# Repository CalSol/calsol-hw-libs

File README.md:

# calsol-hw-libs
CalSol's shared libraries for hardware -- KiCAD libraries and footprints.

## Repository Structure
This is meant to be [submoduled](https://git-scm.com/book/en/v2/Git-Tools-Submodules) into a higher-level project.

- [layout.pretty] - Footprints go here.
- [schematic] - Schematic elements go here.
- [schematic_kicad] - This is a dump of the current KiCAD library set. Don't change these unless you have a compelling reason to (ie. the KiCAD libraries have been updated)

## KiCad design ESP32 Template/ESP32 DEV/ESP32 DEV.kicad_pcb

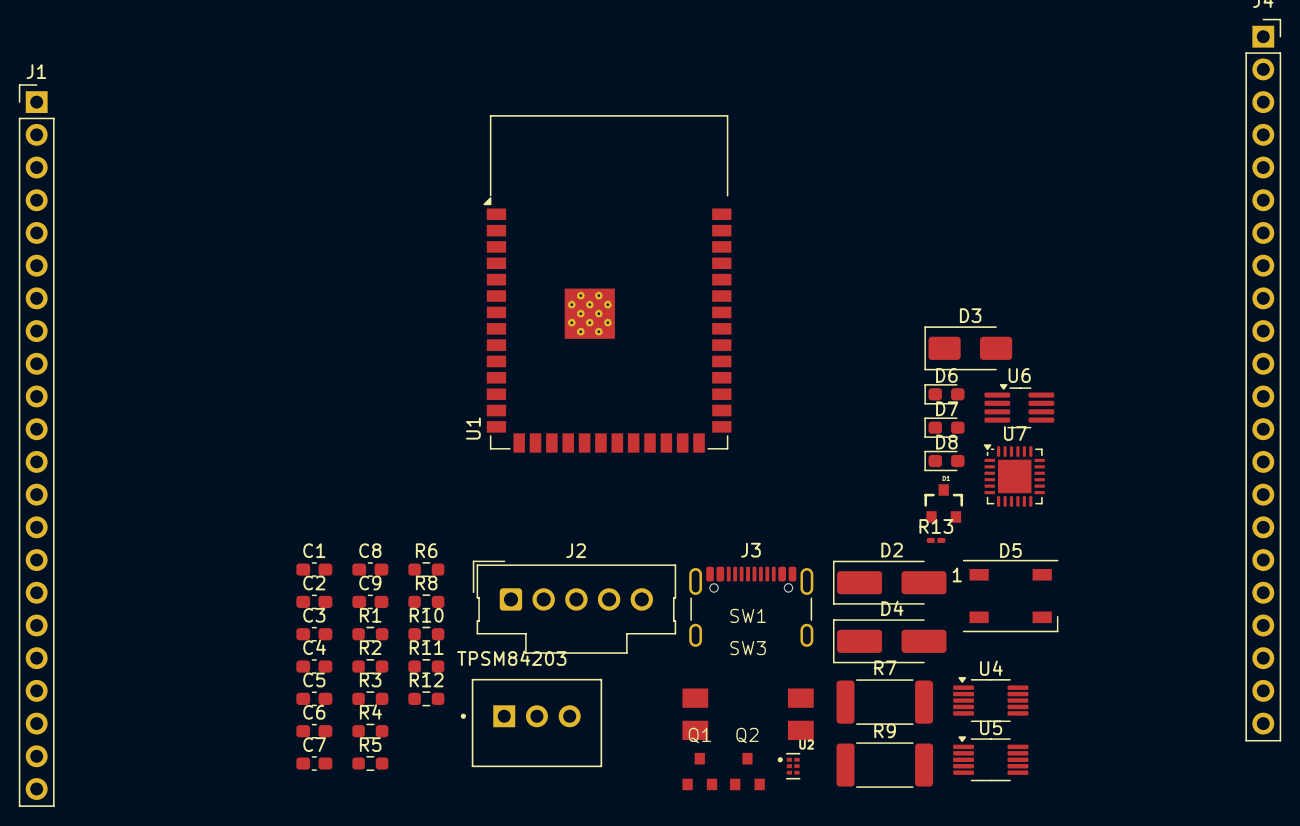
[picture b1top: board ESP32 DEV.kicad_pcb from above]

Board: 2 copper layers, 45 parts (0 on the bottom side), 61 nets, no tracks yet.

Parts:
C1, C8: 100uF; C_0603_1608Metric_Pad1.08x0.95mm_HandSolder
C2, C4, C5, C7: 0.1uF; C_0603_1608Metric_Pad1.08x0.95mm_HandSolder
C3, C6: 10uF; C_0603_1608Metric_Pad1.08x0.95mm_HandSolder
C9: 1uF; C_0603_1608Metric_Pad1.08x0.95mm_HandSolder
D1: PESD1CAN; SOT23-3
D2, D4: D; D_SMA_Handsoldering
D3: SMAJ26CA; D_SMA
D5: WS2812B; LED_WS2812B_PLCC4_5.0x5.0mm_P3.2mm
D6, D7, D8: LED; LED_0603_1608Metric_Pad1.05x0.95mm_HandSolder
J1: Conn_01x22_Pin; PinHeader_1x22_P2.54mm_Vertical
J2: Conn_01x05_Socket; Molex_SL_171971-0005_1x05_P2.54mm_Vertical
J3: USB_C_Receptacle_USB2.0_14P; USB_C_Receptacle_GCT_USB4105-xx-A_16P_TopMnt_Horizontal
J4: Conn_01x22_Pin; PinSocket_1x22_P2.54mm_Vertical
Q1, Q2: NPN; SS8050
R1, R2: 5.1k; R_0603_1608Metric_Pad0.98x0.95mm_HandSolder
R3: 10; R_0603_1608Metric_Pad0.98x0.95mm_HandSolder
R4, R5, R10, R11: 10k; R_0603_1608Metric_Pad0.98x0.95mm_HandSolder
R6: 1k; R_0603_1608Metric_Pad0.98x0.95mm_HandSolder
R7, R9: 0.02; R_2512_6332Metric_Pad1.40x3.35mm_HandSolder
R8: 1K; R_0603_1608Metric_Pad0.98x0.95mm_HandSolder
R12: 220; R_0603_1608Metric_Pad0.98x0.95mm_HandSolder
R13: 220; R_0201_0603Metric_Pad0.64x0.40mm_HandSolder
SW1, SW3: SW_Push; PTS636_SM43_SMTR_LFS
TPSM84203: CONV_TPSM84205EAB
U1: ESP32-S3-WROOM-1
U2: TPD4S012DRYR; PSON50P145X100X60-6N
U4, U5: LTC4151xMS; MSOP-10_3x3mm_P0.5mm
U6: TCAN332; TSOT-23-8_HandSoldering
U7: CP2102N-Axx-xQFN24; QFN-24-1EP_4x4mm_P0.5mm_EP2.6x2.6mm

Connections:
+3.3V: C1.1, C4.1, C6.1, C7.1, C8.1, C9.1, D5.1 (VDD), J1.1, J4.22, R8.1, R10.1, R11.1, R12.2, R13.2, TPSM84203.2 (VOUT), U1.2 (3V3), U6.3 (VCC), U7.5 (VIO), U7.6 (VDD)
+5V: D4.2 (A), J3.A4 (VBUS), J3.A9 (VBUS), J3.B4 (VBUS), J3.B9 (VBUS), J4.21, R3.1, U2.6 (VBUS), U7.7 (VREGIN), U7.8 (VBUS)
+24V: D2.2 (A), D3.1 (A1), J1.20, J2.2, R7.1, U4.1 (SENSE+), U4.2 (VIN), U4.3 (ADR1), U5.2 (VIN)
/24V_out: J1.21, R7.2, U4.10 (SENSE-)
/BC V_in: C3.1, D2.1 (K), D4.1 (K), R9.1, U5.1 (SENSE+), U5.3 (ADR1), U5.4 (ADR0)
/BC V_out: R9.2, TPSM84203.1 (VIN), U5.10 (SENSE-)
/CANH: D1.1, J2.4, U6.7 (CANH)
/CANL: D1.2, J2.5, U6.6 (CANL)
/CC1: J3.A5 (CC1), R1.1
/CC2: J3.B5 (CC2), R2.1
/DTR: Q2.3 (E), R4.1, U7.23 (~DTR)
/D_N: J3.A7 (D-), J3.B7 (D-), U2.2 (D-), U7.4 (D-)
/D_P: J3.A6 (D+), J3.B6 (D+), U2.1 (D+), U7.3 (D+)
/EN: C5.1, J1.2, Q1.1 (C), SW1.2, U1.3 (EN)
/IO0: C2.1, J4.14, Q2.1 (C), SW3.2, U1.27 (IO0)
/IO1: J4.2, U1.39 (IO1)
/IO2: J4.3, U1.38 (IO2)
/IO3: J1.14, U1.15 (IO3)
/IO4: J1.3, U1.4 (IO4)
/IO5: J1.4, U1.5 (IO5)
/IO6: J1.5, U1.6 (IO6)
/IO7: J1.6, U1.7 (IO7)
/IO8: J1.11, U1.12 (IO8)
/IO9: J1.16, U1.17 (IO9)
/IO10: J1.17, U1.18 (IO10)
/IO11: J1.18, U1.19 (IO11)
/IO12: J1.19, U1.20 (IO12)
/IO13: J4.20, U1.21 (IO13)
/IO14: J4.19, U1.22 (IO14)
/IO15: J1.7, U1.8 (IO15)
/IO16/U2RXD: J1.8, U1.9 (IO16), U7.21 (TXD)
/IO17/U2TXD: J1.9, U1.10 (IO17), U7.20 (RXD)
/IO18: J1.10, U1.11 (IO18)
/IO19: J1.12, R6.1, U1.13 (IO19)
/IO20/SDA: J1.13, R10.2, U1.14 (IO20), U4.7 (SDA), U5.7 (SDA)
/IO21/SCL: J4.18, R11.2, U1.23 (IO21), U4.6 (SCL), U5.6 (SCL)
/IO35: J4.13, U1.28 (IO35)
/IO36: J4.12, U1.29 (IO36)
/IO37: J4.11, U1.30 (IO37)
/IO38: J4.10, U1.31 (IO38)
/IO39: J4.9, U1.32 (IO39)
/IO40: J4.8, U1.33 (IO40)
/IO41: J4.7, U1.34 (IO41)
/IO42: J4.6, U1.35 (IO42)
/IO45: J4.15, U1.26 (IO45)
/IO46: J1.15, U1.16 (IO46)
/IO47: J4.17, U1.24 (IO47)
/IO48: J4.16, U1.25 (IO48)
/RTS: Q1.3 (E), R5.1, U7.19 (~RTS)
/RXD: J4.5, U1.36 (RXD0), U6.4 (RXD)
/TXD: J4.4, U1.37 (TXD0), U6.1 (TXD)
GND: C1.2, C2.2, C3.2, C4.2, C5.2, C6.2, C7.2, C8.2, C9.2, D1.3, D3.2 (A2), D5.3 (VSS), D8.1 (K), J1.22, J2.3, J3.A1 (GND), J3.A12 (GND), J3.B1 (GND), J3.B12 (GND), J3.S1 (SHIELD), J4.1, R1.2, R2.2, SW1.1, SW3.1, TPSM84203.3 (GND), U1.1 (GND), U1.40 (GND), U1.41 (GND), U2.4 (GND), U4.4 (ADR0), U4.5 (ADIN), U4.9 (GND), U5.5 (ADIN), U5.9 (GND), U6.2 (GND), U7.2 (GND), U7.25 (GND)
unnamed: D5.4 (DIN), R6.2
unnamed: D6.2 (A), R12.1
unnamed: D6.1 (K), U7.14 (~TXT/GPIO.0)
unnamed: D7.2 (A), R13.1
unnamed: D7.1 (K), U7.13 (~RXT/GPIO.1)
unnamed: D8.2 (A), R8.2
unnamed: Q1.2 (B), R4.2
unnamed: Q2.2 (B), R5.2
unnamed: R3.2, U7.9 (~RST)

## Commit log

2018-02-21 Dump all CalSol generated libraries into repo
2018-02-25 Fix Vicor Pattern
2018-02-26 Created footprint for Bud PN-1335 enclosure outline
2018-02-26 made m4 screw terminal pads wider because previous values were unmanufacturable according to instantdfm
2018-03-02 Added crystal
2018-03-06 Reverted LED
2018-03-06 Added some BMS chips
2018-03-06 Copied over gitignore
2018-03-09 Screw Terminal Update
2018-03-12 Adding Powerpole
2018-03-12 Changed TP silk label to value
2018-03-12 final try adding Maxim ADC
2018-03-12 Added LT3008
2018-04-06 Aux BMS parts
2018-04-06 Order fixed
2018-04-07 Updated power pins
2018-04-16 Added Si4497DY
2018-04-19 Added CTX33-3 and DCU-8 footprint
2018-04-27 Removed DCU-8
2018-05-09 Added SQJ951EP
2018-05-10 Add transformers and 48 pin microcontrollers
2018-05-11 Make a few LPC1517 pins bidirectional
2018-05-27 Make Littelfuse 154 pattern a little easier to solder
2018-05-31 Added AND gate
2018-06-05 Port a few chips from DipTrace
    LQFP-48
    PTS820
    TSSOP-16
2018-06-06 Add in crystal with nicer footprint
2018-06-13 Set pin I/O characteristics correctly
2018-08-25 Add combo discrete SMD and inline header footprints
2018-08-27 libs for training blinky
2019-03-19 Update with Si8621 isolator
2019-04-28 Update default footprint libs
2019-05-06 Add in footprints for various connectors and inductor
2019-05-29 Supercap footprint (maybe someone can find a better name)
2019-07-16 Add iso regulators
2019-07-20 Fix BRAIN library for better ERC sanity Also appears to add SI8621
2019-07-20 Footprint origin of BRAINv3.3 is now in the centre
2019-09-02 Add PN1332 outline
2019-09-05 Add mounting bosses outline
2019-12-09 Add MP pin name to DuraClick mounting pins
2019-12-15 add lt3014b to libs
2019-12-17 update lt3014b
2019-12-23 increase pad size of LT chip footprints
2019-12-23 fix lt3014b to not be a hidden component
2019-12-23 update rgb led footprint to be bigger
2019-12-28 add 3d models to some footprints
2020-01-02 attempt to correct pn-1323 outline to be right angle
2020-01-02 attempt to fix enclosure again
2020-02-06 Fix non-continous board outline on PN-1323
2020-02-12 Add footprint for Calsol logo
2020-02-14 Add Littelfuse OMNI-BLOK 154 fuse holder footprint
2020-02-14 Add Murata DEM8045C series inductor footprint
2020-02-14 Add Wurth M2 SMD threaded spacer footprint
2020-02-14 Add TQFP-144 footprint with 7x7mm pad
2020-02-14 Add Cyclone 10 FPGA schematic symbol
2020-04-12 add more enclosure outlines
2020-04-15 Added in LT8301
2020-04-17 Added WE-MTCI inductor
2020-06-09 updated libs
2021-06-15 Footprint that was uncommitted
2021-08-26 ISE schematic symbol
2021-09-22 Update amplifiers, interface, MCU
2021-10-27 XBee Pro 900HP
2021-10-28 Center some components, add PCF2129
2021-11-21 ERC rules for Si8622 and similar isolators
2021-12-29 Update for 17.5mil x 27.5mil footprint text width and round_rect pads
2021-12-29 Fix 3d lib paths
2021-12-30 add Molex SL right angle THT footprints
2022-02-11 XBee + Supercap + 0603 LED RoundRect + 0606 LED RoundRect
2022-02-15 PCF2129AT (SOIC-20 version of PCF212x)
2022-05-31 KiCAD 6 3d models
2022-05-31 Fix outline for PN-1321, it was not a closed shape
2022-06-02 Reinstate missing things from merges
2022-06-02 CalSol_power => KiCAD6
2022-06-05 Reduce hole ring size to increase clearance from board edge
2022-12-09 CalSol_micro => KiCAD6
    It was bothering me that LPC1549JDB64 was misspelled. It's supposed to be LPC1549JBD64. See? The B and D were swapped. It's all better now.
2023-05-10 Harmonize footprint style and make mfg easier for JLCPCB
2025-02-03 creating template for esp32
